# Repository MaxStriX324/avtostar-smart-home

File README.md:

# AVTOSTAR Home

Модульная система локальной автоматизации для дома и автодома.

**AVTOSTAR — Powered by MaxStriX324**

## Устройства

| Устройство | Назначение | Интерфейсы |
|---|---|---|
| [ESP-12F Debug Module](hardware/esp12f-debug-module/) | Универсальная отладочная плата на ESP8266 | Wi-Fi, ESP-NOW, RS-485, 5 GPIO, ADC |
| [Switch 2](hardware/switch-2/) | Двухклавишный сенсорный выключатель | Wi-Fi, ESP-NOW, RS-485 (WR) |
| [Relay 2](hardware/relay-2/) | Двухканальный модуль управления нагрузками | Wi-Fi, ESP-NOW, RS-485 (WR) |
| [Control](hardware/control/) | Центральный контроллер, локальный веб-интерфейс, сценарии и диагностика | Wi-Fi, RS-485 |

## Архитектура

Switch 2 и Relay 2 обмениваются командами напрямую через ESP-NOW. Для проводной сети используется полудуплексная шина RS-485. Центральный контроллер обеспечивает управление устройствами, сценариями и состояниями через локальный веб-интерфейс.

Настройки, привязки устройств и безопасные состояния выходов хранятся локально. Базовое беспроводное управление не зависит от интернета, маршрутизатора или центрального контроллера.

Для Switch 2 и Relay 2 предусмотрены два варианта комплектации собственной печатной платы:

| Вариант | Wi-Fi / ESP-NOW | RS-485 |
|---|---|---|
| W | Да | — |
| WR | Да | MAX3485 |

## ESP-12F Debug Module v1.0

Универсальный модуль для разработки и отладки аппаратуры и прошивок AVTOSTAR.

| Характеристика | Значение |
|---|---|
| Микроконтроллер | ESP-12F / ESP8266 |
| Приёмопередатчик | MAX3485 |
| Питание | +5 В, AMS1117-3.3 |
| Цифровые выводы | GPIO4, GPIO5, GPIO12, GPIO13, GPIO14 |
| ADC | 0–1 В |
| Сервисный UART | 3,3 В; RESET, FLASH, перемычка RXD–RO |
| Размер PCB | 50 × 35 мм |
| Конструкция | 2 слоя, 1,6 мм, 12 контактов, отверстия Ø0,8 мм |
| Монтаж на материнскую плату | SMD или выводной |

[Описание и распиновка](hardware/esp12f-debug-module/README.md) · [Проект KiCad](hardware/esp12f-debug-module/kicad/) · [BOM](hardware/esp12f-debug-module/BOM.csv) · [Gerber и Excellon](hardware/esp12f-debug-module/manufacturing/AVTOSTAR_ESP12F_50x35_Gerber.zip)

[Общая библиотека KiCad: символы, футпринты и 3D-модели](https://github.com/MaxStriX324/kicad-component-library).

## Документация

| Раздел | Содержание |
|---|---|
| [Аппаратная часть](hardware/) | Платы, проекты и компоненты |
| [Архитектура](docs/architecture.md) | Топология сети, роли устройств и взаимодействие |
| [Требования](docs/requirements.md) | Функции устройств и интерфейсов |
| [Варианты комплектации](docs/variants.md) | W и WR |
| [RS-485](docs/rs485-hardware.md) | Подключение, управление передачей и топология шины |
| [Протокол](docs/protocol.md) | Формат пакета UART/RS-485 и логика обмена |
| [Безопасность](docs/security.md) | Авторизация, привязка и обновление устройств |
| [Прошивки](firmware/) | PlatformIO, сборка и тест кодека |
| [Дорожная карта](docs/roadmap.md) | Этапы разработки |
| [План испытаний](docs/validation-plan.md) | Электрические и функциональные проверки |

## Состояние разработки

На 25.11.2026 опубликованы исходники KiCad, BOM и производственный комплект ESP-12F Debug Module v1.0. Статический аудит проекта и проверка соответствия Gerber и сверловки выполнены. Изготовление, испытания образца и штатный ERC/DRC платы учитываются отдельно в дорожной карте.

Для Switch 2, Relay 2 и Control определены архитектура и требования. В репозитории прошивок доступны конфигурации PlatformIO и кодек тестового пакета; функциональные драйверы и сетевое управление относятся к следующим этапам.

**AVTOSTAR Home — Powered by MaxStriX324.**

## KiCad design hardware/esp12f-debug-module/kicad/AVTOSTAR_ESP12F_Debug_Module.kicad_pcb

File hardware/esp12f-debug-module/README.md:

# AVTOSTAR ESP-12F Debug Module

**Версия 1.0 · AVTOSTAR — Powered by MaxStriX324**

Универсальный отладочный модуль на ESP-12F для подключения к материнской плате. Поддерживает Wi-Fi, ESP-NOW, RS-485, пять цифровых GPIO и аналоговый вход.

## Характеристики

| Параметр | Значение |
|---|---|
| Микроконтроллер | ESP-12F / ESP8266 |
| Приёмопередатчик | MAX3485, SOIC-8 |
| Стабилизатор | AMS1117-3.3 UMW, SOT-223 |
| Основное питание | +5 В |
| Питание логики и UART | +3,3 В |
| Аналоговый вход ADC | 0–1 В |
| Плата | 50 × 35 мм, 1,6 мм, 2 медных слоя |
| Контакты материнской платы | 2 × 6, шаг 2,54 мм, расстояние между рядами 45,72 мм |
| Контактные площадки J2 | 3,2 × 1,6 мм, сверху и снизу; металлизированные отверстия Ø0,8 мм |
| Сервисный разъём J1 | Вертикальный SMD, 1 × 5, шаг 2,54 мм |
| Кнопки | RESET, FLASH |
| Индикация | +5 В, +3,3 В |

## Распиновка J2

| Контакт | Сигнал | Контакт | Сигнал |
|---:|---|---:|---|
| 1 | +5V IN | 2 | GPIO5 / I²C SCL |
| 3 | GND | 4 | GPIO12 / HSPI MISO |
| 5 | +3V3 | 6 | GPIO13 / HSPI MOSI |
| 7 | RS485_A | 8 | GPIO14 / HSPI SCK |
| 9 | RS485_B | 10 | ADC (0–1 В) |
| 11 | GPIO4 / I²C SDA | 12 | GND |

GPIO4/5/12/13/14 работают с логическими уровнями 3,3 В. I²C — программный, HSPI использует GPIO12/13/14; CS назначается на GPIO4 или GPIO5. Делитель ADC располагается на материнской плате. GPIO не допускают прямой подачи 5 В.

## Питание и обвязка ESP-12F

U3 AMS1117-3.3: вывод 1 — GND, 2 и теплоотводящая площадка — +3,3 В, 3 — +5 В. C1 = 100 нФ и C2 = 10 мкФ на входе; C3 = 22 мкФ, 10 В, танталовый и C4 = 100 нФ на выходе. C7 = 10 мкФ и C8 = 100 нФ — питание ESP-12F. Полигоны +3,3 В на обоих медных слоях используются для распределения тепла от выходной теплоотводящей площадки AMS1117. D2 и D3 — индикаторы +5 В и +3,3 В через R4 и R11 по 4,7 кОм.

| Цепь ESP-12F | Подключение |
|---|---|
| RST, вывод 1 | R7 10 кОм к +3,3 В; SW1 RESET на GND |
| EN, вывод 3 | R6 10 кОм к +3,3 В; C9 100 нФ к GND |
| GPIO0, вывод 18 | R8 10 кОм к +3,3 В; SW2 FLASH на GND |
| GPIO2, вывод 17 | R9 10 кОм к +3,3 В |
| GPIO15, вывод 16 | R10 10 кОм к GND |
| GPIO16, вывод 4 | Сигнал MAX, управление RS-485 |
| VCC, вывод 8 | +3,3 В |
| GND, вывод 15 | GND |

GPIO16 используется для управления RS-485; автоматическое пробуждение из Deep Sleep через GPIO16 → RST не предусмотрено.

## RS-485

| Вывод MAX3485 | Подключение |
|---:|---|
| 1 RO | R12 100 Ом → J1.5 (RS485_RO) |
| 2 /RE | MAX (GPIO16) |
| 3 DE | MAX (GPIO16) |
| 4 DI | R5 100 Ом → GPIO1/TXD |
| 5 GND | GND |
| 6 A | R2 10 Ом → RS485_A |
| 7 B | R3 10 Ом → RS485_B |
| 8 VCC | +3,3 В; C5 100 нФ и C6 10 мкФ |

R1 = 10 кОм соединяет MAX с GND. LOW — приём, HIGH — передача. После передачи перевести MAX в LOW только после отправки последнего стоп-бита UART.

D1 SM712 (SOT-23): вывод 1 — RS485_B, вывод 2 — RS485_A, вывод 3 — GND. Терминация 120 Ом устанавливается на двух концах шины на материнских платах. Используется общий сигнальный провод GND.

## Программирование

| J1 | Сигнал |
|---:|---|
| 1 | +3,3 В |
| 2 | GND |
| 3 | TXD ESP-12F → RX программатора |
| 4 | RXD ESP-12F ← TX программатора |
| 5 | RS485_RO |

В режиме RS-485 установлена перемычка J1.4–J1.5. Перед подключением USB-UART её необходимо снять.

1. Подключить GND, TX и RX программатора с логическими уровнями 3,3 В. J1.1 соединён непосредственно с линией +3,3 В. При питании от J2.1 не подключать выход питания программатора.
2. Зажать FLASH, нажать и отпустить RESET, отпустить FLASH.
3. Выполнить прошивку через UART0.
4. Отключить программатор, вернуть перемычку 4–5 и нажать RESET.

## KiCad и подключение к материнской плате

- [Проект KiCad](kicad/AVTOSTAR_ESP12F_Debug_Module.kicad_pro)
- [Принципиальная схема](kicad/AVTOSTAR_ESP12F_Debug_Module.kicad_sch)
- [Печатная плата](kicad/AVTOSTAR_ESP12F_Debug_Module.kicad_pcb)
- [Спецификация компонентов](BOM.csv)
- [Gerber и сверловка 50 × 35 мм](manufacturing/AVTOSTAR_ESP12F_50x35_Gerber.zip)

Библиотека [MaxStriX324 KiCad Component Library](https://github.com/MaxStriX324/kicad-component-library) содержит посадочные места и символы AVTOSTAR:

| Назначение | Имя в библиотеке MaxStriX324 |
|---|---|
| J2 модуля | AVTOSTAR_ESP12F_Module_EdgeSMD_PTH_0.8mm |
| SMD-монтаж на материнскую плату | AVTOSTAR_ESP12F_Debug_Module_SMD |
| Выводной монтаж | AVTOSTAR_ESP12F_Debug_Module_THT |

Металлизированные отверстия J2 Ø0,8 мм предназначены для тонких выводов; максимальный размер квадратного вывода — 0,5 мм. Антенна ESP-12F располагается в верхней части платы и выступает за её верхний край. В зоне антенны исключаются медь, дорожки, переходные отверстия и компоненты; остальные участки материнской платы доступны для разводки.

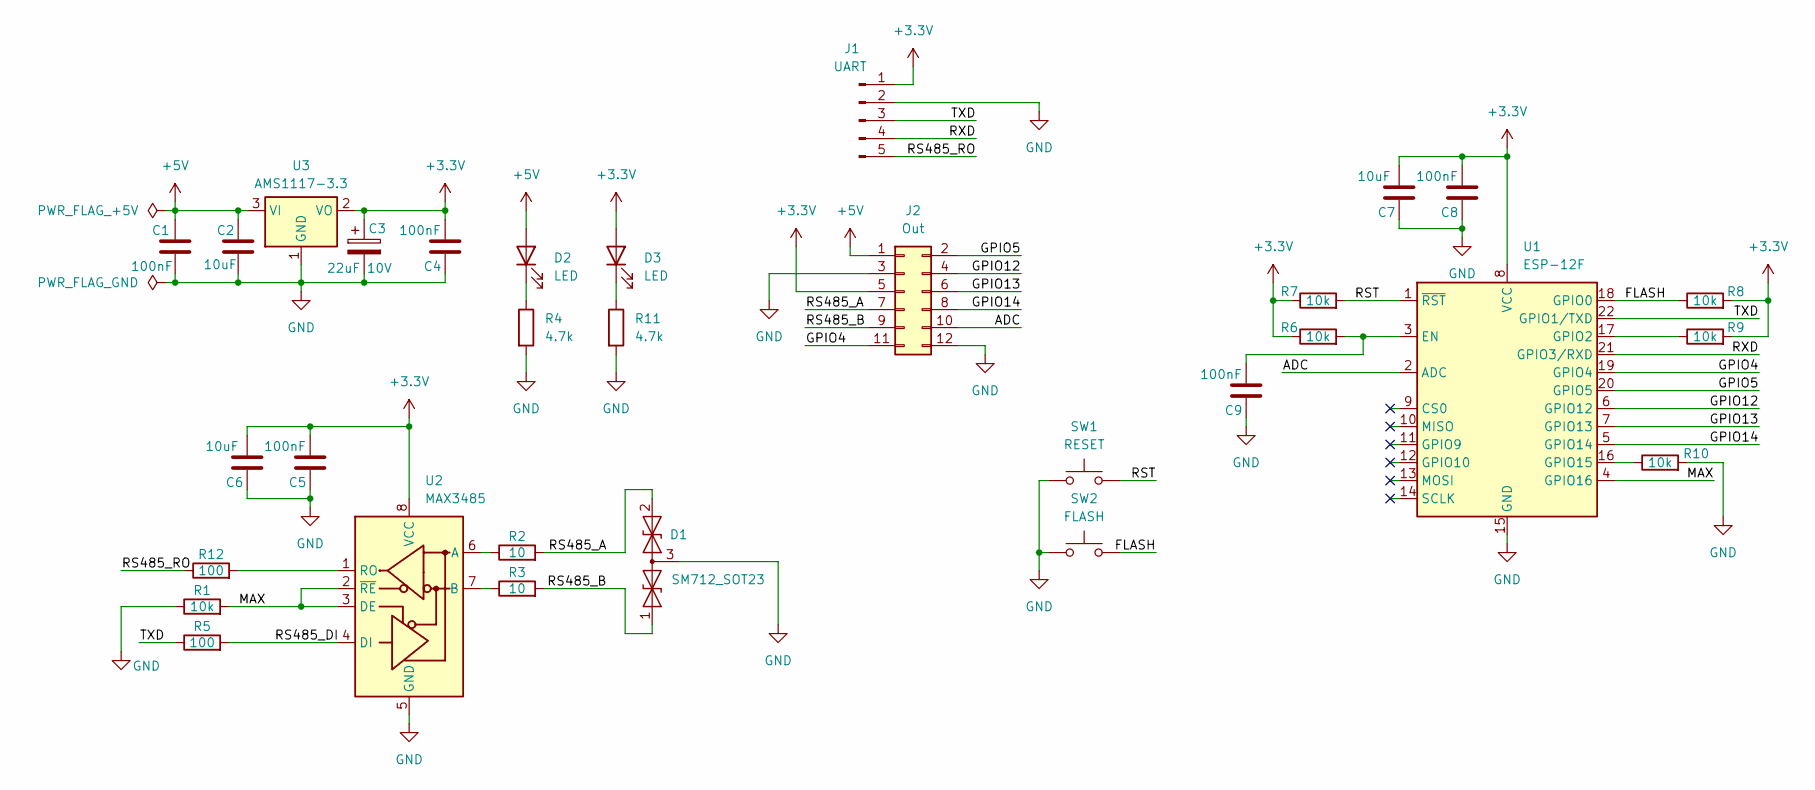
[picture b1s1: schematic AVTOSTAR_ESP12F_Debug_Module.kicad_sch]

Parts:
C1, C4, C5, C8, C9: 100nF; C_0805_2012Metric
C2: 10uF; C_1206_3216Metric
C3: 22uF 10V; CP_EIA-3528-21_Kemet-B
C6, C7: 10uF; C_0805_2012Metric
D1: SM712_SOT23; SOT-23
D2, D3: LED; LED_0805_2012Metric
J1: UART; PinHeader_1x05_P2.54mm_Vertical_SMD_Pin1Left
J2: Out; AVTOSTAR_ESP12F_Module_EdgeSMD_PTH_0.8mm
R1, R6, R7, R8, R9, R10: 10k; R_0805_2012Metric
R2, R3: 10; R_0805_2012Metric
R4, R11: 4.7k; R_0805_2012Metric
R5, R12: 100; R_0805_2012Metric
SW1: RESET; SW_Tactile_SPST_NO_Straight_CK_PTS636Sx25SMTRLFS
SW2: FLASH; SW_Tactile_SPST_NO_Straight_CK_PTS636Sx25SMTRLFS
U1: ESP-12F; ESP-12E
U2: MAX3485; SOIC-8_3.9x4.9mm_P1.27mm
U3: AMS1117-3.3; SOT-223-3_TabPin2

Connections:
+3.3V: C3.1, C4.2, C5.2, C6.2, C7.2, C8.2, D3.2 (A), J1.1, J2.5, R6.1, R7.1, R8.2, R9.2, U1.8 (VCC), U2.8 (VCC), U3.2 (VO)
+5V: C1.2, C2.2, D2.2 (A), J2.1, U3.3 (VI)
/ADC: J2.10, U1.2 (ADC)
/FLASH: R8.1, SW2.2, U1.18 (GPIO0)
/GPIO4: J2.11, U1.19 (GPIO4)
/GPIO5: J2.2, U1.20 (GPIO5)
/GPIO12: J2.4, U1.6 (GPIO12)
/GPIO13: J2.6, U1.7 (GPIO13)
/GPIO14: J2.8, U1.5 (GPIO14)
/MAX: R1.2, U1.4 (GPIO16), U2.2 (~RE), U2.3 (DE)
/RS485_A: D1.2 (A2), J2.7, R2.2
/RS485_B: D1.1 (A1), J2.9, R3.2
/RS485_DI: R5.2, U2.4 (DI)
/RS485_RO: J1.5, R12.1
/RST: R7.2, SW1.2, U1.1 (~RST)
/RXD: J1.4, U1.21 (GPIO3/RXD)
/TXD: J1.3, R5.1, U1.22 (GPIO1/TXD)
GND: C1.1, C2.1, C3.2, C4.1, C5.1, C6.1, C7.1, C8.1, C9.1, D1.3 (common), J1.2, J2.3, J2.12, R1.1, R4.2, R10.2, R11.2, SW1.1, SW2.1, U1.15 (GND), U2.5 (GND), U3.1 (GND)
unnamed: D2.1 (K), R4.1
unnamed: D3.1 (K), R11.1
unnamed: C9.2, R6.2, U1.3 (EN)
unnamed: R9.1, U1.17 (GPIO2)
unnamed: R10.1, U1.16 (GPIO15)
unnamed: R2.1, U2.6 (A)
unnamed: R3.1, U2.7 (B)
unnamed: R12.2, U2.1 (RO)

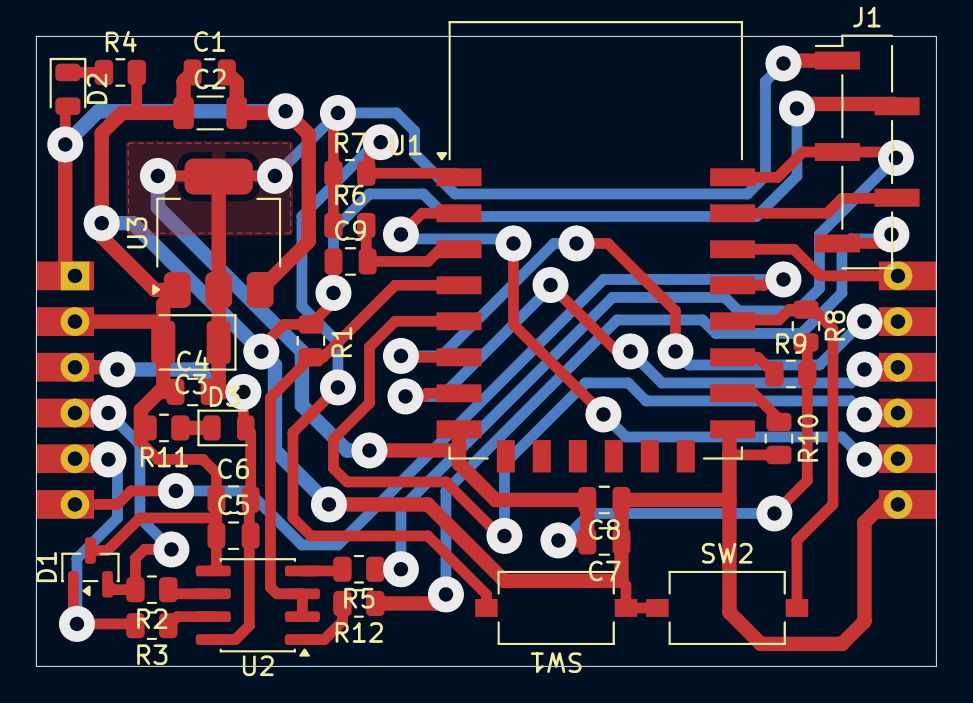
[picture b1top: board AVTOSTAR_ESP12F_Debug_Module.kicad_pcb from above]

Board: 2 copper layers, 50.0 x 35.0 mm, 31 parts (0 on the bottom side), 26 nets.

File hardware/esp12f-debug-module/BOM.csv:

"Reference","Qty","Value","DNP","Exclude from BOM","Exclude from Board","Footprint","Datasheet"
"C1,C4,C5,C8,C9","5","100nF","","","","Capacitor_SMD:C_0805_2012Metric",""
"C2","1","10uF","","","","Capacitor_SMD:C_1206_3216Metric",""
"C3","1","22uF 10V","","","","Capacitor_Tantalum_SMD:CP_EIA-3528-21_Kemet-B",""
"C6,C7","2","10uF","","","","Capacitor_SMD:C_0805_2012Metric",""
"D1","1","SM712_SOT23","","","","Package_TO_SOT_SMD:SOT-23","https://www.littelfuse.com/~/media/electronics/datasheets/tv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"
"D2,D3","2","LED","","","","LED_SMD:LED_0805_2012Metric",""
"J1","1","UART","","","","Connector_PinHeader_2.54mm:PinHeader_1x05_P2.54mm_Vertical_SMD_Pin1Left",""
"J2","1","Out","","","","MaxStriX324:AVTOSTAR_ESP12F_Module_EdgeSMD_PTH_0.8mm",""
"R1,R6,R7,R8,R9,R10","6","10k","","","","Resistor_SMD:R_0805_2012Metric",""
"R2,R3","2","10","","","","Resistor_SMD:R_0805_2012Metric",""
"R4,R11","2","4.7k","","","","Resistor_SMD:R_0805_2012Metric",""
"R5,R12","2","100","","","","Resistor_SMD:R_0805_2012Metric",""
"SW1","1","RESET","","","","Button_Switch_SMD:SW_Tactile_SPST_NO_Straight_CK_PTS636Sx25SMTRLFS",""
"SW2","1","FLASH","","","","Button_Switch_SMD:SW_Tactile_SPST_NO_Straight_CK_PTS636Sx25SMTRLFS",""
"U1","1","ESP-12F","","","","RF_Module:ESP-12E","http://wiki.ai-thinker.com/_media/esp8266/esp8266_series_mod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"
"U2","1","MAX3485","","","","Package_SO:SOIC-8_3.9x4.9mm_P1.27mm","https://datasheets.maximintegrated.com/en/ds/MAX3483-MAX3491.pdf"
"U3","1","AMS1117-3.3","","","","Package_TO_SOT_SMD:SOT-223-3_TabPin2","http://www.advanced-monolithic.com/pdf/ds1117.pdf"
